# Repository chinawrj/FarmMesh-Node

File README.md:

# FarmMesh Node

**An integrated hardware and software solution for farm-wide Mesh networking**

English | [简体中文](README.zh-CN.md)

[Overview](#overview) · [Solution scope](#solution-scope-and-current-progress) · [A1 hardware](#a1-hardware-prototype) · [Features & targets](#key-features-and-performance-targets) · [Architecture](#architecture) · [Internal interface](#candidate-internal-interface) · [Wireless research](#wireless-research-status) · [Open decisions](#open-decisions) · [Roadmap](#roadmap) · [Contact](#contact-and-participation) · [References](#references)

## Overview

**FarmMesh Node is a hardware and software project for a complete farm wireless networking solution.** Its scope includes node electronics, embedded firmware, communication protocols, Mesh networking, client and sensor access, and system integration and field validation. Hardware and software are developed together toward the same farm-wide service goals; the A1 PCB is the current hardware milestone within that larger project.

FarmMesh Node aims to provide **farm-wide coverage using solar-powered infrastructure nodes that need no pre-installed power or network cabling**, combining on-demand high-speed client access with distributed access for hundreds to approximately 1,000 low-traffic sensors. Inter-node links are intended to be entirely wireless. Solar supply, storage and node power budgets remain to be designed; this is not a claim of all-weather energy autonomy, and a gateway/uplink may still be needed.

The client-access design target is **50 Mbps of effective throughput after connecting to a Mesh node**, available on demand wherever needed in the farm. The initial capacity assumption is **1–2 concurrent high-speed clients across the whole farm**, not per infrastructure node and not a limit on the number of Mesh nodes or total clients. This does not require every location to receive 50 Mbps simultaneously. Measurement endpoints, direction and test conditions remain TBD; there is no guarantee of 50 Mbps across multiple Mesh hops or to the Internet.

Infrastructure nodes are intended to provide **concurrent BLE or Wi-Fi access for several hundred to approximately 1,000 low-traffic, low-power sensors across the whole farm**, distributed among multiple Mesh nodes. This is an aggregate planning target requiring capacity validation, not 1,000 direct BLE connections per node or simultaneous packet transmission by every sensor. End-device energy requirements and the infrastructure's solar-power budget are separate concerns; neither implies that the forwarding infrastructure must sleep. Low Wi-Fi traffic alone does not establish low power consumption, and BLE/Wi-Fi coexistence requires validation.

Each infrastructure node contains **one RP2350B and three ESP32-C5 chips**, implemented in A1 with three official **ESP32-C5-WROOM-1U-N8R8 modules**. The RP2350B is intended to aggregate and forward data inside the node, with an independent internal link to each C5. The separate preliminary **50 Mbps per internal link** target is a hardware design input, not a demonstrated user throughput figure or proof that the access-service target can be met. Its directional and raw-rate/payload-rate definitions remain TBD.

Development is staged from the node hardware foundation through firmware and network software to full-system validation. The **A1 prototype has eight schematic sheets, a four-layer PCB and a manufacturing package released for controlled engineering prototypes**; its release record is [RELEASE.md](hardware/rev-a/RELEASE.md). Firmware and network software implementation remain pending. Coverage, user throughput, terminal capacity, power consumption and sustained internal-link performance have not been measured.

## Solution scope and current progress

| Area | Role in the complete solution | Current progress |
| --- | --- | --- |
| Node hardware | RP2350B and three ESP32-C5 modules, power, PCB, antennas and physical interfaces | A1 design and reviewed manufacturing package available; assembly and bring-up pending; deployment solar power remains to be designed |
| Embedded firmware | RP2350 PIO/DMA and C5 PARLIO drivers, framing, buffering, flow control and coordination across the three links | Hardware pin assignments frozen for A1; firmware and interface timing validation pending |
| Network software | Inter-node wireless transport, Mesh protocol and routing, Wi-Fi/BLE client and sensor access, configuration and diagnostics | Requirements and wireless research recorded; protocol selection and implementation pending |
| System integration | Hardware/firmware/network integration, power and RF coexistence, throughput, sensor capacity and farm deployment | Staged first-board test plan available; multi-node and field validation planned |

This repository currently contains the hardware release, system requirements and wireless research. Software will be developed as part of the same project; the table distinguishes the intended solution from what is already implemented.

## A1 hardware prototype

A1 contains a 100 × 100 mm four-layer PCB, protected single-cell nominal 3.7 V Li-ion input, 3.3 V buck-boost supply, RP2350B, three C5 modules, independent parallel interfaces, UART download headers and RP USB/SWD. USB data disconnects in hardware when VBUS is absent, including ROM BOOTSEL operation. USB does not power or charge the board. Solar charging and storage sizing remain separate design work.

| Artifact | Use and status |
| --- | --- |
| [Release status](hardware/rev-a/RELEASE.md) | Authoritative prototype fabrication gate and validation boundaries |
| [Manufacturing ZIP](hardware/rev-a/FarmMesh-Node-A1-manufacturing.zip) / [SHA-256](hardware/rev-a/FarmMesh-Node-A1-manufacturing.zip.sha256) | Released for controlled A1 prototypes: Gerber, drills, BOM, placements, drawings, editable source and review evidence |
| [KiCad project](hardware/rev-a/FarmMesh-Node.kicad_pro) / [PCB](hardware/rev-a/FarmMesh-Node.kicad_pcb) | Editable native sources; download the repository together with project-local libraries |
| [Eight-page schematic PDF](hardware/rev-a/review/FarmMesh-Node-A1.pdf) | A1 circuit review copy |
| [Manufacturing instructions](hardware/rev-a/FABRICATION.md) / [parts selection](hardware/rev-a/parts-selection.json) | Stackup, assembly requirements, 153 selected assembly parts and accessories |
| [First-board test plan](hardware/rev-a/FIRST-BOARD-TEST.md) | Staged power, debug, USB, thermal, load and RF checks; results are not yet measured |
| [Design notes](hardware/rev-a/DESIGN-NOTES.md) | Circuit and layout choices, sources and reproducibility |
| [Power review](hardware/rev-a/reports/a1-power-review.md) / [RF and digital review](hardware/rev-a/reports/a1-rf-digital-review.md) / [DFM and BOM review](hardware/rev-a/reports/a1-dfm-bom-review.md) | Independent engineering review records, with remaining bench-validation boundaries |

The C5 modules use external dual-band antennas. Their native USB pins are allocated to PARLIO; each C5 retains UART download and logging. **No wireless transport or Mesh protocol is selected by the hardware.** A fabrication-ready package does not establish RF, power or throughput performance.

## Key features and performance targets

**Targets below are planned requirements, not measured results.** TBD means to be determined. Chip resource facts and candidate allocations are identified separately.

| Item | Target or configuration | Status and boundaries |
| --- | --- | --- |
| Solar power and deployment | Solar-capable infrastructure nodes; no pre-installed power or network cables; wireless inter-node links | Design goal; solar sizing, storage and node power budget TBD; energy autonomy unverified; gateway/uplink architecture open |
| Farm-wide coverage | Wireless access throughout the farm | Product goal; area, terrain, range, node count and placement TBD |
| On-demand high-speed access | 50 Mbps effective client-access throughput after connecting to a Mesh node | Design goal; measurement endpoints, direction and conditions TBD; no multi-hop or Internet throughput guarantee |
| High-speed client concurrency | Initially 1–2 across the whole farm | Capacity assumption, unverified; not per Mesh node, a Mesh-node count limit or a total-client limit |
| Concurrent low-traffic access | Several hundred to approximately 1,000 sensors across the farm via BLE or Wi-Fi | Aggregate planning target, distributed across nodes; capacity has an upper bound and needs validation; not per-node BLE sessions or simultaneous packets from all sensors |
| Per-node BLE capacity | Bounded by C5 controller, host stack/configuration and radio scheduling | Connection-based versus advertising/scanning mode TBD; role and per-node limits unconfirmed; three C5 capacities cannot simply be added into a guarantee |
| End-device energy use | Support low-power terminal operation | Product goal; activity duty cycle, power budget and battery-life target TBD; solar infrastructure budget separately TBD |
| Node composition | 1 × RP2350B + 3 × ESP32-C5-WROOM-1U-N8R8 | Selected A1 architecture; physical validation pending |
| A1 hardware artifacts | Eight-sheet KiCad schematic, four-layer PCB and selected BOM; nominal 3.7 V single-cell Li-ion input | Fabrication gate in RELEASE.md; solar charging, firmware and physical validation remain separate |
| Independent internal links | Preliminary target: 50 Mbps per C5–RP2350 link, not shared across three links | Internal-interface target; direction, raw versus payload rate and required margin for the user-service target TBD; unverified |
| Internal interface | PARLIO ↔ PIO, separate 4-bit TX/RX buses; both clocks supplied by C5 | Candidate; 12 signals per link; A1 pin assignment drawn and reviewed; programs and timing unverified |
| RP2350B resources | 48 Bank0 GPIOs; 3 PIO blocks / 12 state machines; 32 shared instructions per block; 16 system DMA channels | Chip resource facts; preliminary interface allocation below is not implementation proof |
| Wireless roles and interconnection | Three C5 chips per node; Mesh protocol, radio roles/channels and gateway/uplink TBD | Architecture decisions pending; no guaranteed BLE/Wi-Fi coexistence performance or Internet throughput |

## Architecture

### Network concept

The diagram separates end-device access from the Mesh infrastructure. Dotted lines show intended service relationships and node membership, not physical radio links or packet paths. The service box is a logical grouping, not a central device. Inter-node topology, radio roles and Mesh protocol remain open; the measurement endpoint and gateway/uplink boundary are also TBD.

```mermaid
flowchart TB
    fast["High-speed clients / 高速客户端<br/>50 Mbps access target / 接入目标<br/>1–2 concurrent farm-wide / 全网并发目标"]
    low["Low-traffic sensors / 低流量传感器<br/>Hundreds to approx. 1,000 farm-wide / 全网数百至约千个<br/>Concurrent access goal / 并发接入目标"]
    mesh["FarmMesh infrastructure services / 基础设施服务层<br/>Logical grouping / 逻辑分组"]
    fast -.- mesh
    low -.-|"BLE or Wi-Fi / 计划接入"| mesh
    subgraph infra["Solar-capable Mesh nodes / 太阳能 Mesh 节点目标"]
        a["FarmMesh Node A"]
        b["FarmMesh Node B"]
        c["FarmMesh Node C"]
    end
    mesh -.- a
    mesh -.- b
    mesh -.- c
    deployment["No pre-installed power or network cables / 免预布电源线或网线<br/>Wireless inter-node links / 节点间纯无线目标"]
    deployment -.- mesh
    boundary["Measurement endpoint and gateway/uplink / 测速端点与网关或上联<br/>TBD / 待定"]
    mesh -.- boundary
```

### Inside one node

Each line represents an independent internal data link. Clock and VALID directions are defined separately in the interface table below; the arrows here do not specify clock sources.

```mermaid
flowchart LR
    subgraph node["One FarmMesh Node / 单个节点"]
        rp["RP2350B · PIO + system DMA<br/>Data aggregation and forwarding / 数据汇聚与转发"]
        ca["ESP32-C5 A · PARLIO"]
        cb["ESP32-C5 B · PARLIO"]
        cc["ESP32-C5 C · PARLIO"]
        rp <-->|"Link A / 链路 A"| ca
        rp <-->|"Link B / 链路 B"| cb
        rp <-->|"Link C / 链路 C"| cc
    end
```

The three ESP32-C5 chips' wireless roles, channels and connections to other nodes are not assigned by this diagram.

### Wireless coexistence boundary

Espressif documents shared RF resources with time-division and priority arbitration. Its current C5 coexistence table marks Wi-Fi SoftAP Connecting/Connected combined with BLE Scan/Advertising/Connected as C1 (supported, with unstable performance). This is a constraint to validate if a C5 is assigned both Wi-Fi AP and BLE roles; it does not establish that the three-chip node cannot meet its goals. Radio-role allocation and coexistence must be checked against the selected SDK and operating scenarios. Concurrent terminal service does not imply independent, simultaneous full-load radios on a single C5. See the [official RF coexistence guide](https://docs.espressif.com/projects/esp-idf/en/stable/esp32c5/api-guides/coexist.html#supported-coexistence-scenario-for-esp32-c5).

Per-node BLE capacity has an implementation-dependent limit, not one universal fixed connection count imposed by the BLE specification. The C5 controller and NimBLE host expose separate connection-limit settings in the [official configuration reference](https://docs.espressif.com/projects/esp-idf/en/stable/esp32c5/api-reference/kconfig-reference.html#config-bt-le-max-connections). Connection-based access and connectionless advertising/scanning are different [BLE roles and topologies](https://docs.espressif.com/projects/esp-idf/en/stable/esp32c5/api-guides/ble/get-started/ble-introduction.html#bluetooth-le-network-topology); scanning advertisements must not be counted as persistent connections. Advertising/scanning terminal capacity needs its own validation. Select the access mode and three C5 roles before confirming per-node capacity; simply adding three chip-level limits does not establish node capacity.

## Candidate internal interface

The selected hardware interface is **ESP32-C5 PARLIO ↔ RP2350 PIO**, using separate 4-bit TX and RX data buses. A1 freezes the physical connections; firmware and timing for concurrent bidirectional operation remain unvalidated.

**Each C5 supplies both clocks. The RP2350 PIO follows an external clock in both directions**, including when the RP2350 sends data to the C5.

| Transfer direction | DATA | Clock | VALID |
| --- | --- | --- | --- |
| C5 → RP2350 | 4 signals, C5 → RP | C5 TX CLK → RP | C5 TX VALID → RP |
| RP2350 → C5 | 4 signals, RP → C5 | C5 RX CLK → RP | RP VALID → C5 |

This uses **12 signals per link**: 8 DATA, 2 CLK and 2 VALID. Three links use **36 signals**, plus a common ground reference. A1 freezes the prototype pin assignment in the schematics and [C5 pinmap](hardware/rev-a/c5-pinmap.json); firmware and hardware timing validation remain open.

PARLIO has separate TX and RX units. A shared-data, half-duplex alternative would require explicit output-enable, tri-state and direction-change handling. PARLIO must not be treated as an automatically reversing shared bus, and disabling TX does not by itself establish a high-impedance output.

### Preliminary resource budget

| RP2350B resource | Available | Initial three-link estimate |
| --- | --- | --- |
| Bank0 GPIO, QFN80 package | 48 | 36 interface signals; 12 remain before other allocations |
| PIO state machines | 12 across 3 PIO blocks | 6: one RX and one TX per link |
| System DMA channels | 16 | 6: one per direction per link |
| PIO instruction memory | 32 shared instructions per PIO block | Program size not yet established |

These estimates do not constitute an implemented PIO program or validated timing design. A1 assigns the three interfaces to RP2350B GPIO0–35. Each PIO has a 32-GPIO window selected by GPIOBASE 0 or 16; the PIO configuration and instruction use still need implementation checks. Dedicated QSPI storage pins, USB and SWD do not consume the 48 Bank0 GPIOs. Other board functions use part of the remaining GPIO budget. The 30-GPIO RP2350A cannot accommodate this 36-signal candidate.

### Processing responsibilities and timing boundary

- **CPU:** initialization, buffer preparation, transaction coordination and exception handling.
- **PIO:** beat-level sampling and output timing under the C5-provided clocks.
- **System DMA:** block transfers between PIO FIFOs and RP2350 SRAM, intended to avoid CPU byte-by-byte copying.

The C5 PARLIO RX documentation describes receive-clock output and VALID-based reception gating. C5 RX/GDMA transactions must be prepared before data arrives; VALID alone does not create a receive transaction. The RP must prepare the first beat and drive VALID correctly. Start/end behavior, sampling edges and gating timing still require a concrete design and validation.

Frame boundaries, DMA rearming and sustained operation also remain to be designed. A ring-address setting alone is not a guarantee of indefinite operation, and this draft does not claim CPU-free transfer management.

## Wireless research status

The [wireless link research notes](docs/wireless-link-research.md) record the **2026-09-22** review, official sources, version-specific binary observations and MTU/MSS constraints. **No wireless transport has been selected.** The client-access targets and internal hardware candidate above remain unchanged.

| Topic | Current finding | Status and boundary |
| --- | --- | --- |
| WDS / four-address bridge | Direct public C5 support not confirmed in the reviewed documentation/API | Does not establish a hardware impossibility |
| ESP-NOW and public raw TX | Different frame/payload limits; neither establishes this project's 50 Mbps effective throughput | Research candidates; no sustained-throughput validation |
| Rate and power controls | Public per-peer ESP-NOW rate configuration and per-C5 Wi-Fi maximum-power ceiling | Documented controls; no confirmed ready-to-enable ESP-NOW automatic-rate tool; custom adaptation remains future work |
| AP+STA + proxy ARP | Currently not pursued | Project direction, not a technical impossibility finding |

## Open decisions

1. Define the client-to-Mesh-node 50 Mbps access test: measurement endpoints, uplink/downlink direction and conditions. Start with 1–2 concurrent high-speed clients farm-wide; multi-hop and Internet throughput remain outside any established guarantee.
2. Define each internal link's 50 Mbps target separately: one direction, both directions combined, or each direction; raw rate versus effective payload rate; and the capacity margin needed to support the user-service goal.
3. Establish three-link PIO feasibility, clock/timing constraints, GPIO mapping, instruction budget and required CPU participation. Define first-beat readiness, VALID behavior, receive-transaction preparation, frame boundaries and DMA rearming.
4. Validate the farm-wide planning target of several hundred to approximately 1,000 low-traffic sensors. Select connection-based BLE versus advertising/scanning roles, establish per-node limits and define activity duty cycles, traffic, latency and end-device energy targets. Radio roles/channels and BLE/Wi-Fi coexistence remain to be validated.
5. Design the solar supply, storage and infrastructure power budget for deployment without pre-installed power or network cabling. Later, decide Mesh protocol and routing, antennas, coverage area/terrain and deployment, gateway/uplink, environmental protection and the full BOM.

These decisions guide the complete hardware and software solution. The current repository establishes the A1 hardware foundation and records the software design inputs; firmware, network protocols, routing and system optimization are the next development stages.

## Roadmap

| Phase | Scope | Status |
| --- | --- | --- |
| 1 | System requirements and hardware/software architecture | Service targets and A1 hardware allocation recorded; software architecture and protocols remain open |
| 2 | A1 schematics, PCB and manufacturing package | Released for controlled engineering prototypes; see RELEASE.md |
| 3 | Board bring-up, drivers and internal-link firmware | Awaiting assembled boards; firmware and timing validation pending |
| 4 | Network software, Mesh routing and client/sensor services | Planned; integrate with validated node hardware and firmware |
| 5 | Multi-node integration and farm deployment | Planned; validate coverage, throughput, sensor capacity, power and reliability |

## Contact and participation

Interested in FarmMesh Node? Use [GitHub Issues](https://github.com/chinawrj/FarmMesh-Node/issues) to discuss requirements, hardware, firmware, network software, system testing or ways to participate. You can also visit the project owner's [GitHub profile](https://github.com/chinawrj).

## References

Official sources for subsequent design checks:

- [RP2350 datasheet](https://datasheets.raspberrypi.com/rp2350/rp2350-datasheet.pdf) — GPIO, PIO and system DMA resources.
- [ESP32-C5 datasheet](https://documentation.espressif.com/esp32-c5_datasheet_en.html) and [technical reference manual](https://documentation.espressif.com/esp32-c5_technical_reference_manual_en.pdf) — device and peripheral details.
- [ESP32-C5 PARLIO RX driver](https://docs.espressif.com/projects/esp-idf/en/stable/esp32c5/api-reference/peripherals/parlio/parlio_rx.html) — receive clock, VALID and transaction setup.
- [ESP32-C5 PARLIO TX driver](https://docs.espressif.com/projects/esp-idf/en/stable/esp32c5/api-reference/peripherals/parlio/parlio_tx.html) — transmit configuration and operation.
- [ESP32-C5 RF coexistence](https://docs.espressif.com/projects/esp-idf/en/stable/esp32c5/api-guides/coexist.html) — supported role combinations and shared RF scheduling constraints.

Differences in maximum full-duplex width descriptions across C5 documentation still need reconciliation. This draft considers only the 4-bit-per-direction candidate and makes no claim about wider full-duplex configurations. The ESP-IDF `stable` links can change; record the selected SDK and document versions when the implementation baseline is set.

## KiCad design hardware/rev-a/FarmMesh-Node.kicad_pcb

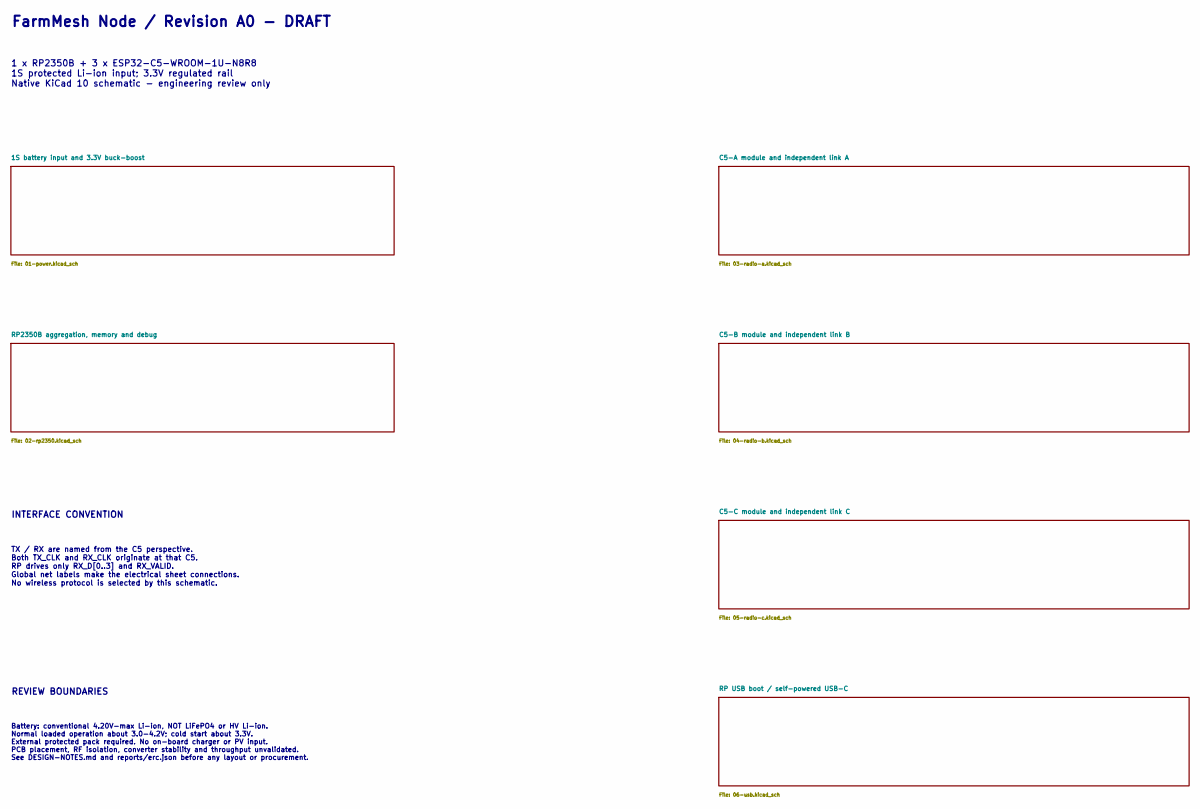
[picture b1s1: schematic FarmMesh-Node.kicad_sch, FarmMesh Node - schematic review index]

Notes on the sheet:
Battery: conventional 4.20V-max Li-ion, NOT LiFePO4 or HV Li-ion. Normal loaded operation about 3.0-4.2V; cold start about 3.3V. External protected pack required. No on-board charger or PV input. PCB placement, RF isolation, converter stability and throughput unvalidated. See DESIGN-NOTES.md and re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
INTERFACE CONVENTION
TX / RX are named from the C5 perspective. Both TX_CLK and RX_CLK originate at that C5. RP drives only RX_D[0..3] and RX_VALID. Global net labels make the electrical sheet connections. No wireless protocol is selected by this schematic.
REVIEW BOUNDARIES
1 x RP2350B + 3 x ESP32-C5-WROOM-1U-N8R8 1S protected Li-ion input; 3.3V regulated rail Native KiCad 10 schematic - engineering review only
FarmMesh Node / Revision A0 - DRAFT

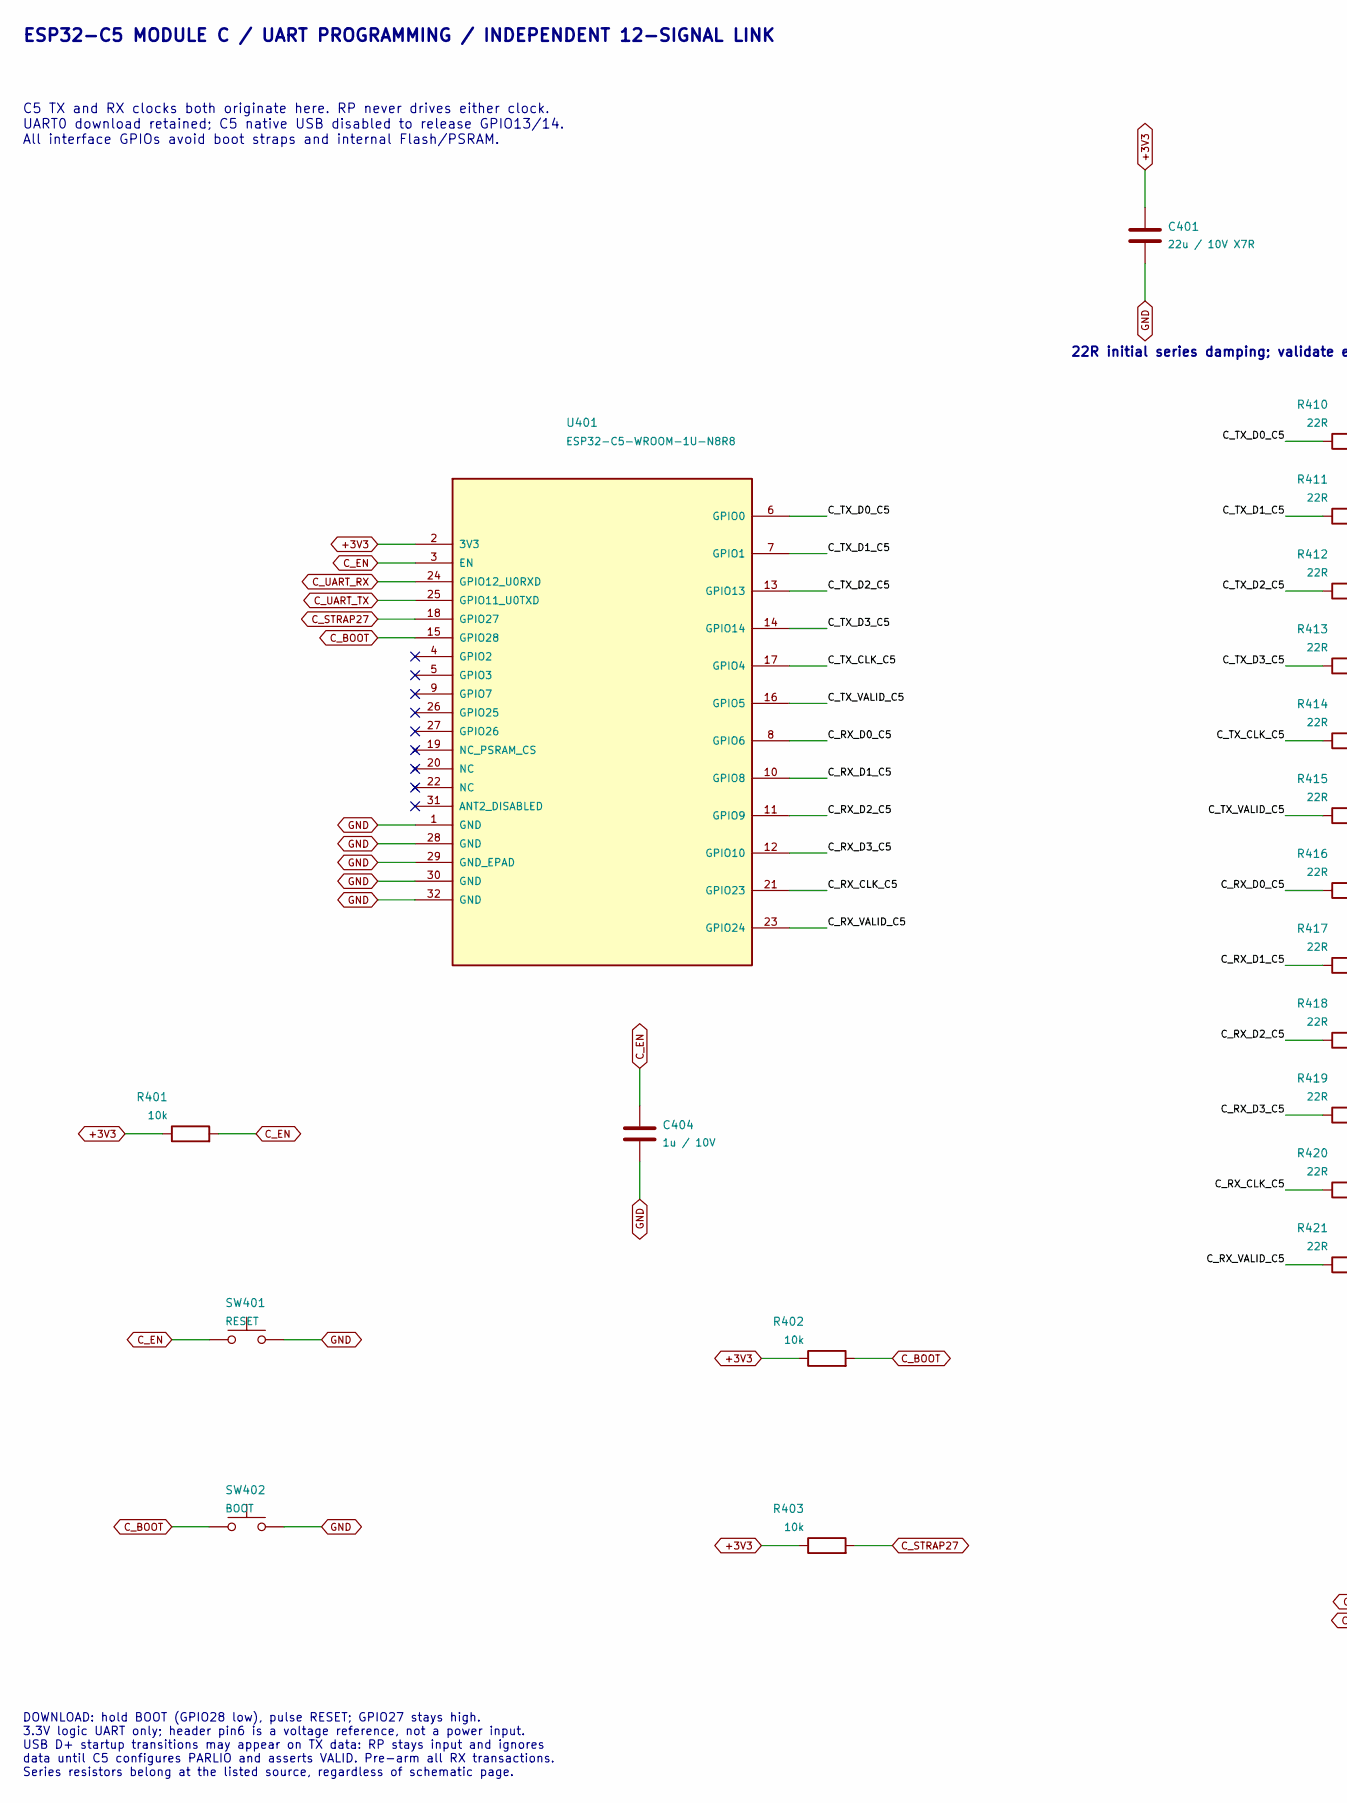
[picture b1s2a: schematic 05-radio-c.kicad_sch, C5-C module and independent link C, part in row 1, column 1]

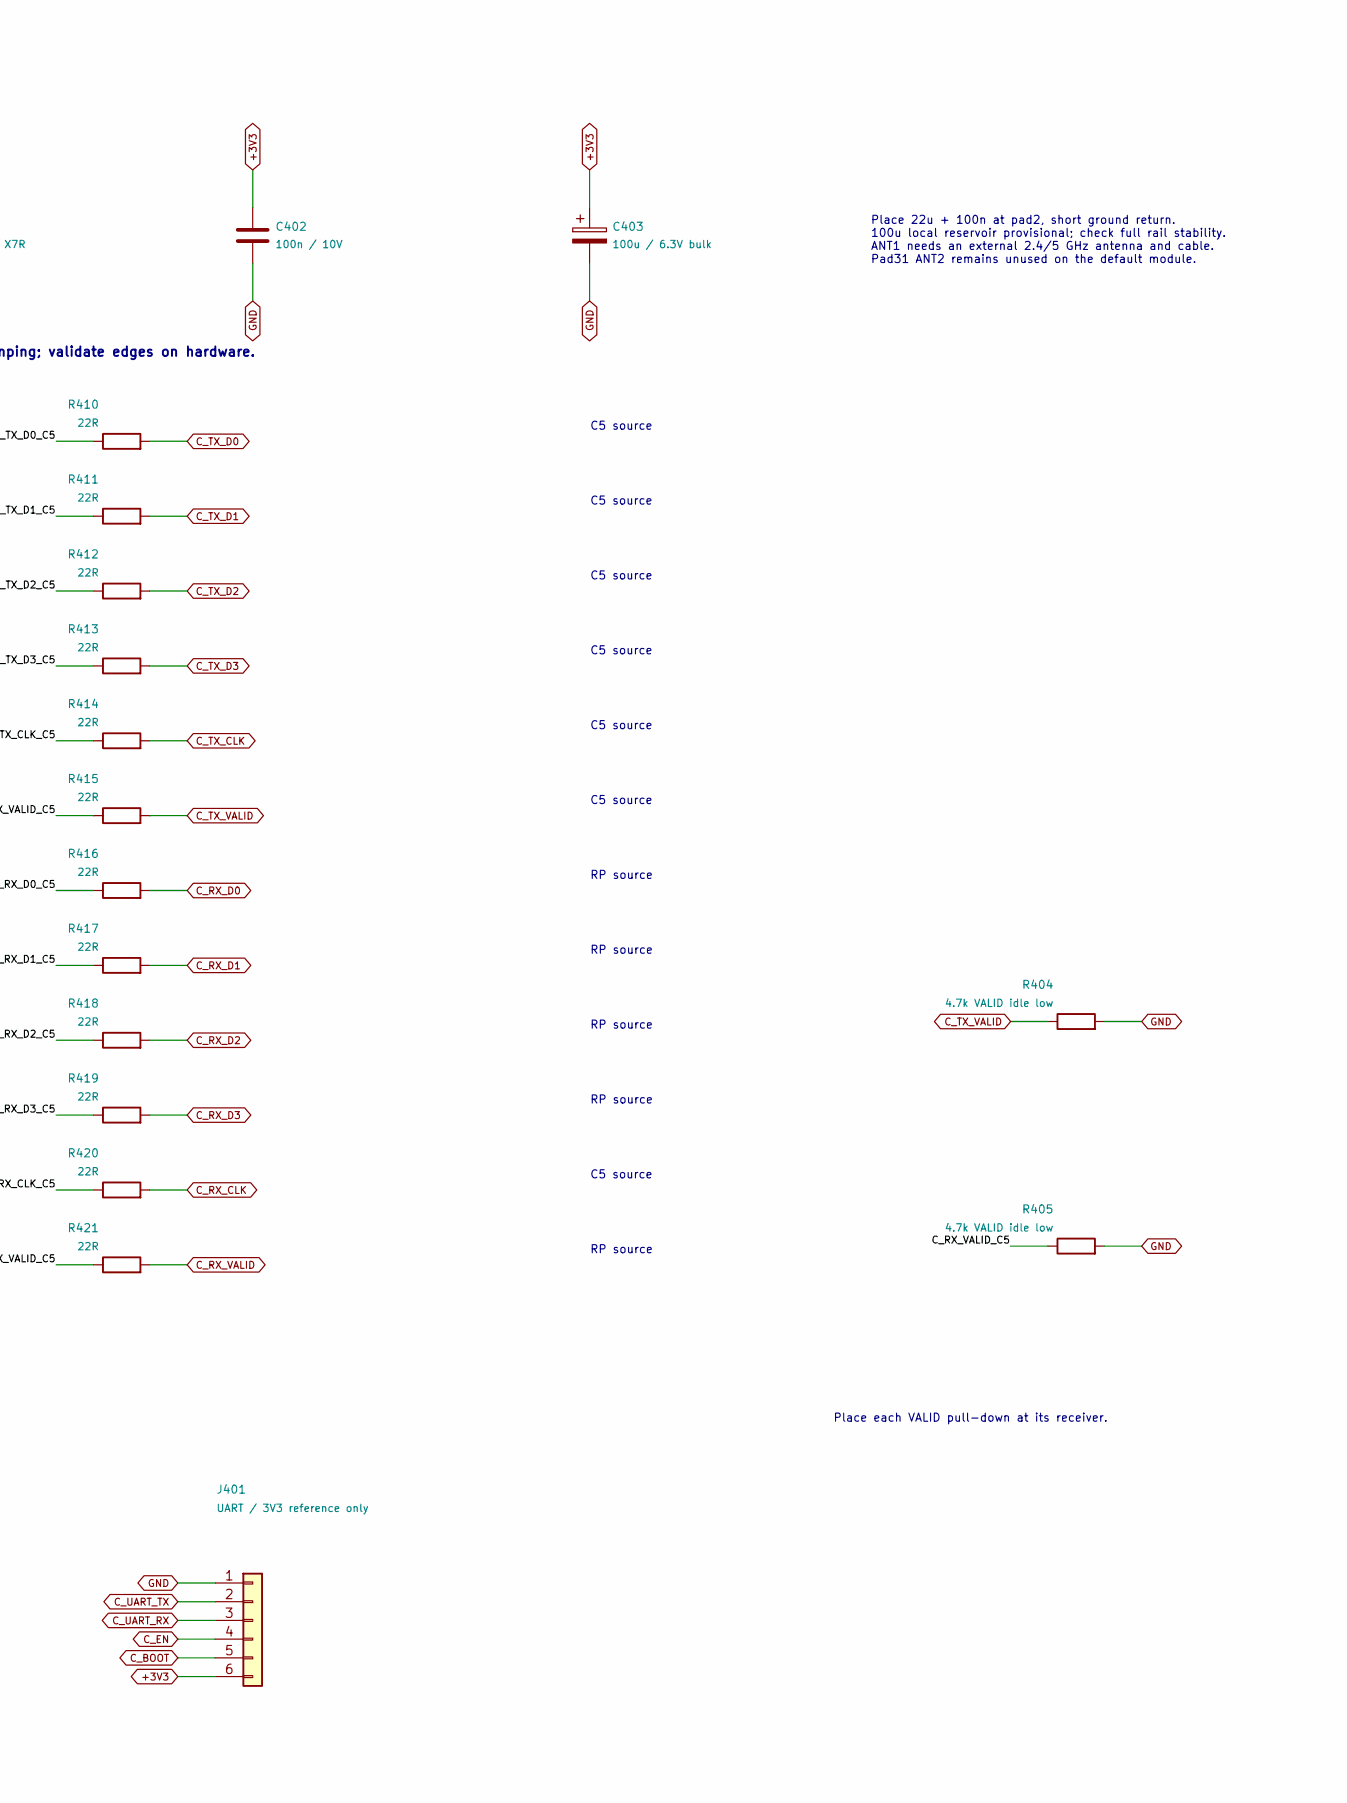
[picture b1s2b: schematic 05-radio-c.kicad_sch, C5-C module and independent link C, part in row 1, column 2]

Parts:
C401: 22u / 10V X7R; C_0805_2012Metric
C402: 100n / 10V; C_0603_1608Metric
C403: 100u / 6.3V bulk; CP_Elec_6.3x5.8
C404: 1u / 10V; C_0603_1608Metric
J401: UART / 3V3 reference only; PinHeader_1x06_P2.54mm_Vertical
R401, R402, R403: 10k; R_0603_1608Metric
R404, R405: 4.7k VALID idle low; R_0603_1608Metric
R410, R411, R412, R413, R414, R415, R416, R417, R418, R419, R420, R421: 22R; R_0603_1608Metric
SW401: RESET; SW_Push_1P1T_NO_E-Switch_TL3301NxxxxxG
SW402: BOOT; SW_Push_1P1T_NO_E-Switch_TL3301NxxxxxG
U401: ESP32-C5-WROOM-1U-N8R8; ESP32-C5-WROOM-1U; MPN ESP32-C5-WROOM-1U-N8R8

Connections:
+3V3: C401.1, C402.1, C403.1, J401.6, R401.1, R402.1, R403.1, U401.2 (3V3); also elsewhere on the board
/C5-C module and independent link C/C_RX_CLK_C5: R420.1, U401.21 (GPIO23)
/C5-C module and independent link C/C_RX_D0_C5: R416.1, U401.8 (GPIO6)
/C5-C module and independent link C/C_RX_D1_C5: R417.1, U401.10 (GPIO8)
/C5-C module and independent link C/C_RX_D2_C5: R418.1, U401.11 (GPIO9)
/C5-C module and independent link C/C_RX_D3_C5: R419.1, U401.12 (GPIO10)
/C5-C module and independent link C/C_RX_VALID_C5: R405.1, R421.1, U401.23 (GPIO24)
/C5-C module and independent link C/C_TX_CLK_C5: R414.1, U401.17 (GPIO4)
/C5-C module and independent link C/C_TX_D0_C5: R410.1, U401.6 (GPIO0)
/C5-C module and independent link C/C_TX_D1_C5: R411.1, U401.7 (GPIO1)
/C5-C module and independent link C/C_TX_D2_C5: R412.1, U401.13 (GPIO13)
/C5-C module and independent link C/C_TX_D3_C5: R413.1, U401.14 (GPIO14)
/C5-C module and independent link C/C_TX_VALID_C5: R415.1, U401.16 (GPIO5)
C_BOOT: J401.5, R402.2, SW402.1, U401.15 (GPIO28)
C_EN: C404.1, J401.4, R401.2, SW401.1, U401.3 (EN)
C_RX_CLK: R420.2; also elsewhere on the board
C_RX_D0: R416.2; also elsewhere on the board
C_RX_D1: R417.2; also elsewhere on the board
C_RX_D2: R418.2; also elsewhere on the board
C_RX_D3: R419.2; also elsewhere on the board
C_RX_VALID: R421.2; also elsewhere on the board
C_STRAP27: R403.2, U401.18 (GPIO27)
C_TX_CLK: R414.2; also elsewhere on the board
C_TX_D0: R410.2; also elsewhere on the board
C_TX_D1: R411.2; also elsewhere on the board
C_TX_D2: R412.2; also elsewhere on the board
C_TX_D3: R413.2; also elsewhere on the board
C_TX_VALID: R404.1, R415.2; also elsewhere on the board
C_UART_RX: J401.3, U401.24 (GPIO12_U0RXD)
C_UART_TX: J401.2, U401.25 (GPIO11_U0TXD)
GND: C401.2, C402.2, C403.2, C404.2, J401.1, R404.2, R405.2, SW401.2, SW402.2, U401.1 (GND), U401.28 (GND), U401.29 (GND_EPAD), U401.30 (GND), U401.32 (GND); also elsewhere on the board

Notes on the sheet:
RP source
C5 source
C5 TX and RX clocks both originate here. RP never drives either clock. UART0 download retained; C5 native USB disabled to release GPIO13/14. All interface GPIOs avoid boot straps and internal Flash/PSRAM.
ESP32-C5 MODULE C / UART PROGRAMMING / INDEPENDENT 12-SIGNAL LINK
Place 22u + 100n at pad2, short ground return. 100u local reservoir provisional; check full rail stability. ANT1 needs an external 2.4/5 GHz antenna and cable. Pad31 ANT2 remains unused on the default module.
DOWNLOAD: hold BOOT (GPIO28 low), pulse RESET; GPIO27 stays high. 3.3V logic UART only; header pin6 is a voltage reference, not a power input. USB D+ startup transitions may appear on TX data: RP stays input and ignores data until C5 configures PARLIO and asserts VALID. Pre-arm all RX transactions.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
Place each VALID pull-down at its receiver.
22R initial series damping; validate edges on hardware.

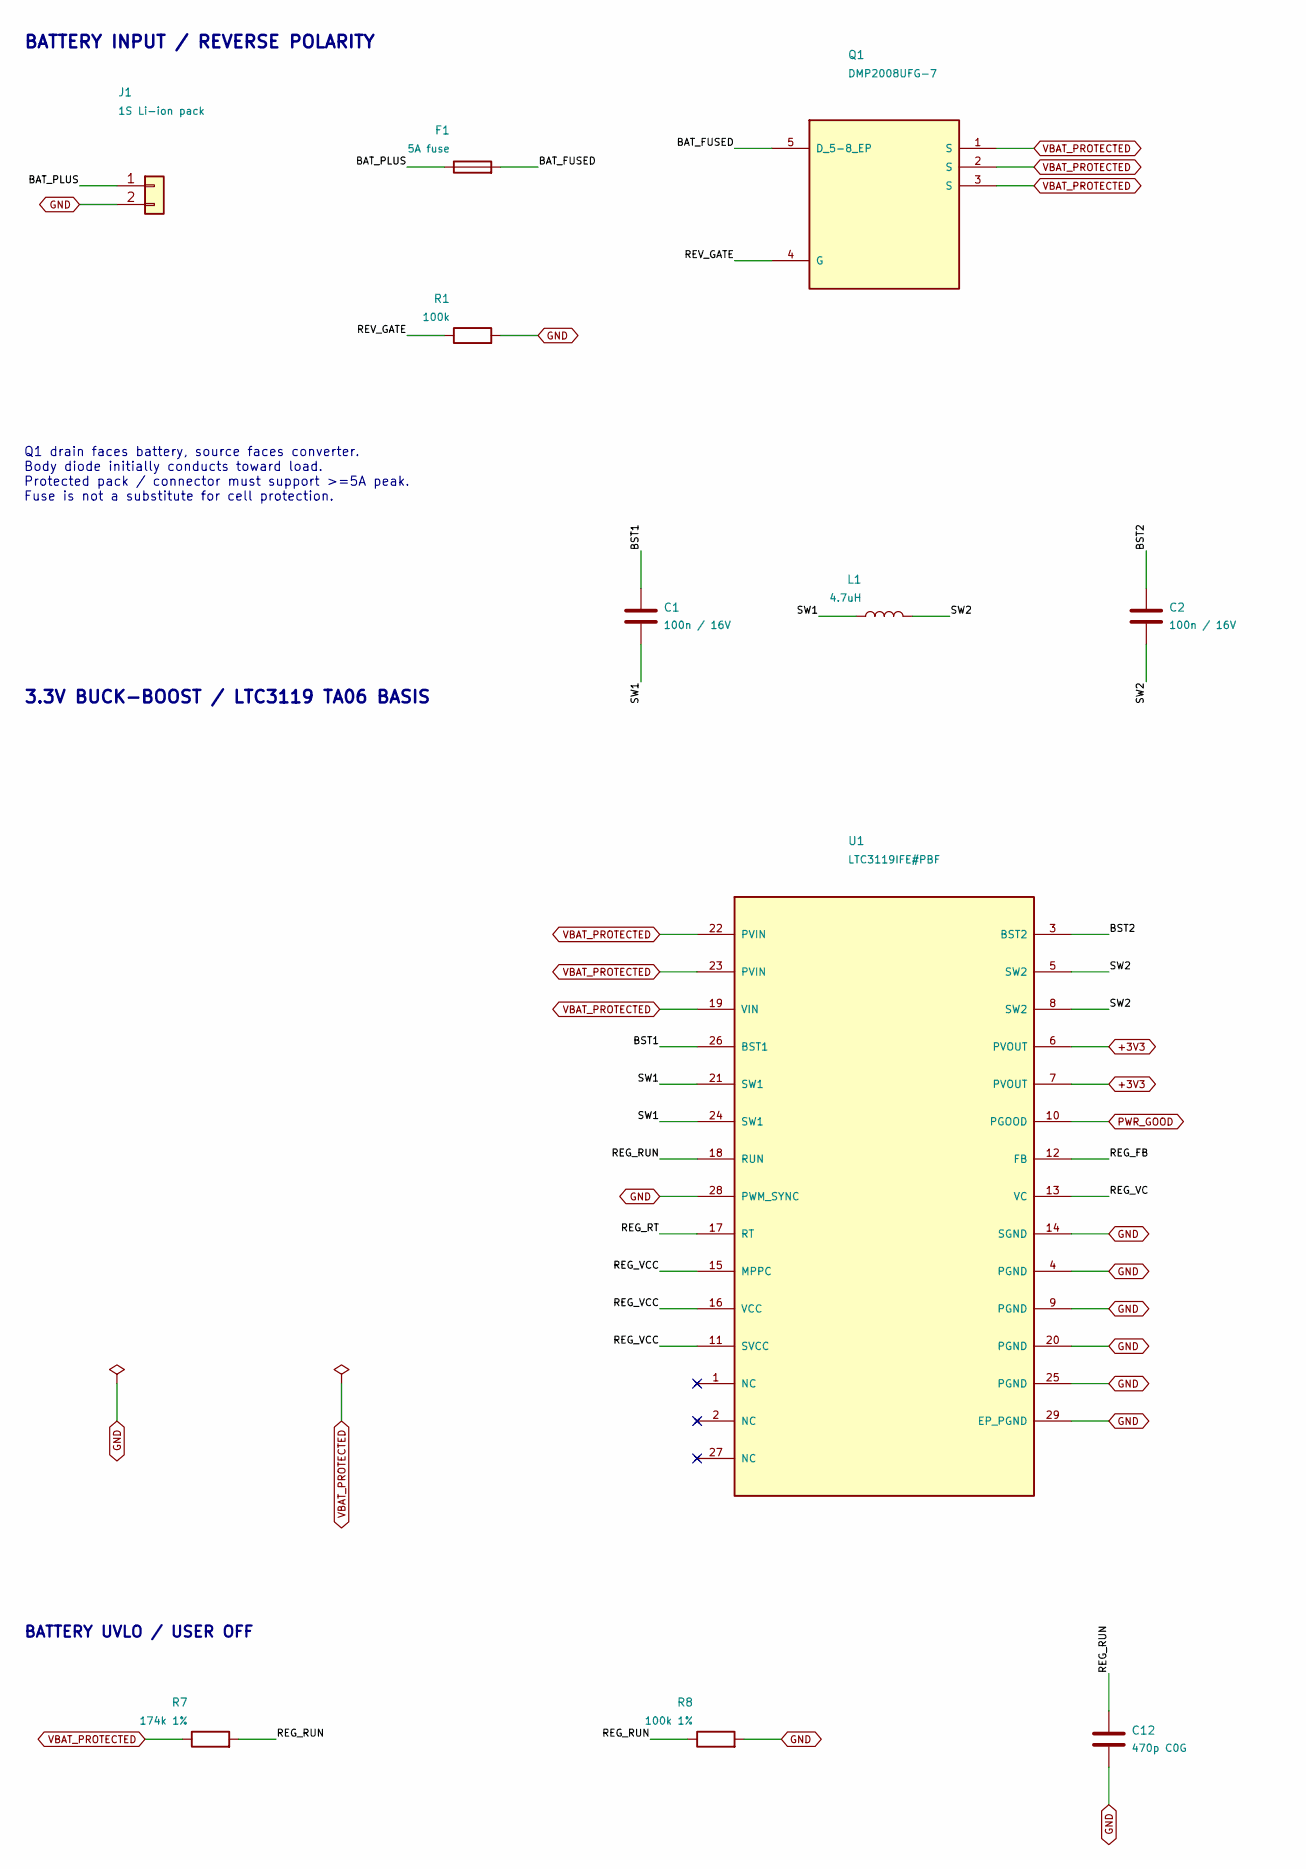
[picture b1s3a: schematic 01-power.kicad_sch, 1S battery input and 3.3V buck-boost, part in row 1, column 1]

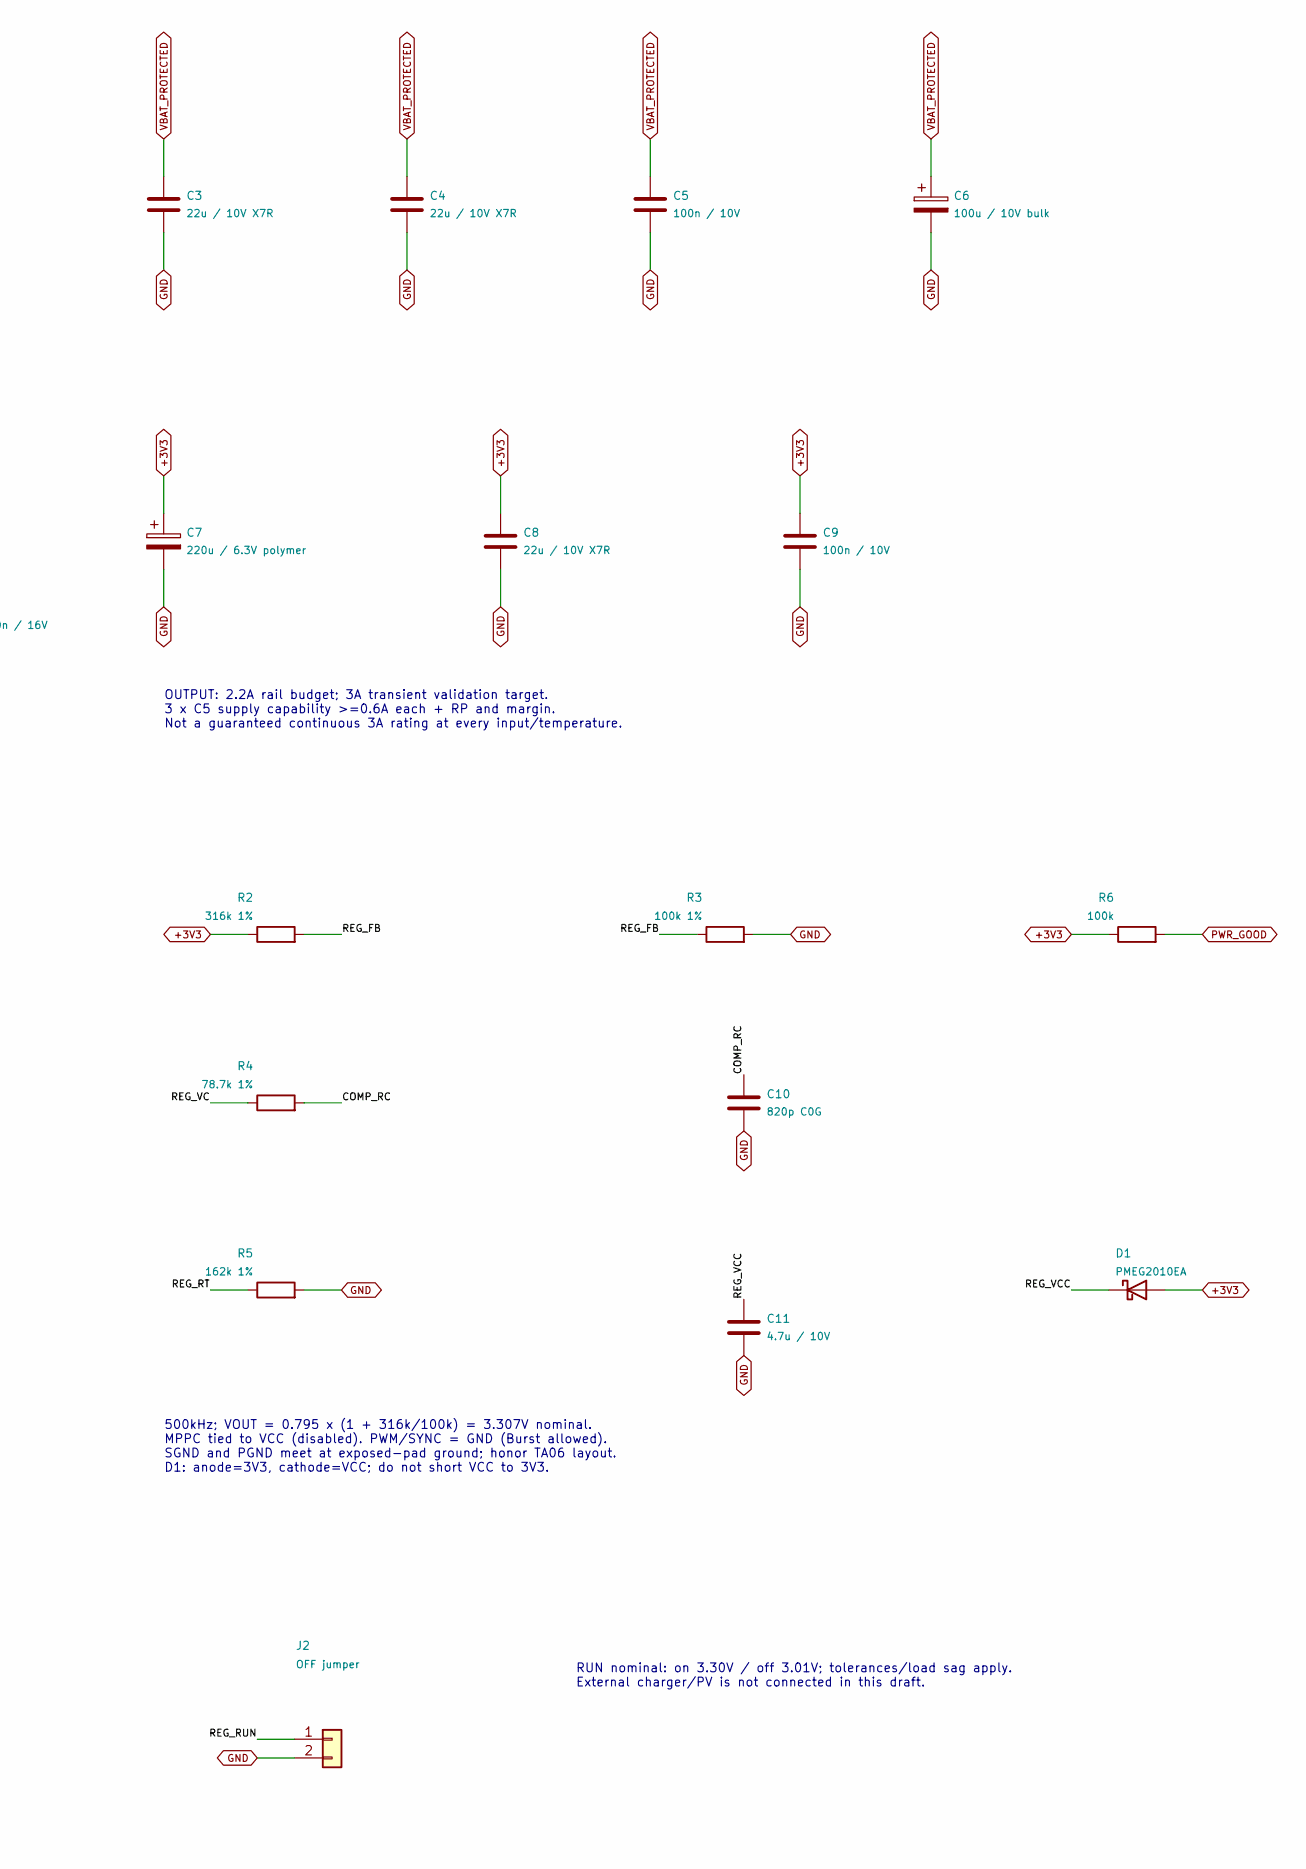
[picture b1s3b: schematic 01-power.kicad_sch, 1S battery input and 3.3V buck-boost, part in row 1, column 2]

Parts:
C1, C2: 100n / 16V; C_0603_1608Metric
C3, C4, C8: 22u / 10V X7R; C_0805_2012Metric
C5, C9: 100n / 10V; C_0603_1608Metric
C6: 100u / 10V bulk; CP_Elec_6.3x5.8
C7: 220u / 6.3V polymer; CP_Elec_6.3x5.9; MPN 6SVPE220M
C10: 820p C0G; C_0603_1608Metric
C11: 4.7u / 10V; C_0805_2012Metric
C12: 470p C0G; C_0603_1608Metric
D1: PMEG2010EA; D_SOD-323; MPN PMEG2010EA,115
F1: 5A fuse; Fuse_Littelfuse-NANO2-451_453; MPN 0451005.MRL
J1: 1S Li-ion pack; JST_VH_B2P-VH_1x02_P3.96mm_Vertical; MPN B2P-VH(LF)(SN)
J2: OFF jumper; PinHeader_1x02_P2.54mm_Vertical
L1: 4.7uH; L_Coilcraft_XAL7070-XXX; MPN XAL7070-472MEC
Q1: DMP2008UFG-7; Diodes_PowerDI3333-8; MPN DMP2008UFG-7
R1, R6: 100k; R_0603_1608Metric
R2: 316k 1%; R_0603_1608Metric
R3, R8: 100k 1%; R_0603_1608Metric
R4: 78.7k 1%; R_0603_1608Metric
R5: 162k 1%; R_0603_1608Metric
R7: 174k 1%; R_0603_1608Metric
U1: LTC3119IFE#PBF; TSSOP-28-1EP_4.4x9.7mm_P0.65mm_EP3.05x7.56mm; MPN LTC3119IFE#PBF

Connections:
+3V3: C7.1, C8.1, C9.1, D1.2 (A), R2.1, R6.1, U1.6 (PVOUT), U1.7 (PVOUT); also elsewhere on the board
/1S battery input and 3.3V buck-boost/BAT_FUSED: F1.2, Q1.5 (D_5-8_EP)
/1S battery input and 3.3V buck-boost/BAT_PLUS: F1.1, J1.1
/1S battery input and 3.3V buck-boost/BST1: C1.1, U1.26 (BST1)
/1S battery input and 3.3V buck-boost/BST2: C2.1, U1.3 (BST2)
/1S battery input and 3.3V buck-boost/COMP_RC: C10.1, R4.2
/1S battery input and 3.3V buck-boost/REG_FB: R2.2, R3.1, U1.12 (FB)
/1S battery input and 3.3V buck-boost/REG_RT: R5.1, U1.17 (RT)
/1S battery input and 3.3V buck-boost/REG_RUN: C12.1, J2.1, R7.2, R8.1, U1.18 (RUN)
/1S battery input and 3.3V buck-boost/REG_VC: R4.1, U1.13 (VC)
/1S battery input and 3.3V buck-boost/REG_VCC: C11.1, D1.1 (K), U1.11 (SVCC), U1.15 (MPPC), U1.16 (VCC)
/1S battery input and 3.3V buck-boost/REV_GATE: Q1.4 (G), R1.1
/1S battery input and 3.3V buck-boost/SW1: C1.2, L1.1, U1.21 (SW1), U1.24 (SW1)
/1S battery input and 3.3V buck-boost/SW2: C2.2, L1.2, U1.5 (SW2), U1.8 (SW2)
GND: C3.2, C4.2, C5.2, C6.2, C7.2, C8.2, C9.2, C10.2, C11.2, C12.2, J1.2, J2.2, R1.2, R3.2, R5.2, R8.2, U1.4 (PGND), U1.9 (PGND), U1.14 (SGND), U1.20 (PGND), U1.25 (PGND), U1.28 (PWM_SYNC), U1.29 (EP_PGND); also elsewhere on the board
PWR_GOOD: R6.2, U1.10 (PGOOD); also elsewhere on the board
VBAT_PROTECTED: C3.1, C4.1, C5.1, C6.1, Q1.1 (S), Q1.2 (S), Q1.3 (S), R7.1, U1.19 (VIN), U1.22 (PVIN), U1.23 (PVIN); also elsewhere on the board

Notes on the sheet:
3.3V BUCK-BOOST / LTC3119 TA06 BASIS
BATTERY INPUT / REVERSE POLARITY
Q1 drain faces battery, source faces converter. Body diode initially conducts toward load. Protected pack / connector must support >=5A peak. Fuse is not a substitute for cell protection.
OUTPUT: 2.2A rail budget; 3A transient validation target. 3 x C5 supply capability >=0.6A each + RP and margin. Not a guaranteed continuous 3A rating at every input/temperature.
RUN nominal: on 3.30V / off 3.01V; tolerances/load sag apply. External charger/PV is not connected in this draft.
BATTERY UVLO / USER OFF
500kHz; VOUT = 0.795 x (1 + 316k/100k) = 3.307V nominal. MPPC tied to VCC (disabled). PWM/SYNC = GND (Burst allowed). SGND and PGND meet at exposed-pad ground; honor TA06 layout. D1: anode=3V3, cathode=VCC; do not short VCC to 3V3.

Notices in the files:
parts and their libraries:
Derived from KiCad Connector_USB USB4105-xx-A; CC-BY-SA-4.0 with KiCad exception.
